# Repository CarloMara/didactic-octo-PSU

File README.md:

# **Didactic PSU**

**An efficient finals project**

So, @nicogela and I decided to build a LAB PSU, but because we're lazy people and we don't like to carry weight we're tring to unite the high efficiency of the switching topologies to the high stability and low noise of the linear ones.

Up until now we've designed the linear stage, and we added to it some DACs in oreder to controll it with a uC. The next stage in the design process will be the testing of the linear + the dacs. If everithing works we will go ahead adding to the desing the switching stage.

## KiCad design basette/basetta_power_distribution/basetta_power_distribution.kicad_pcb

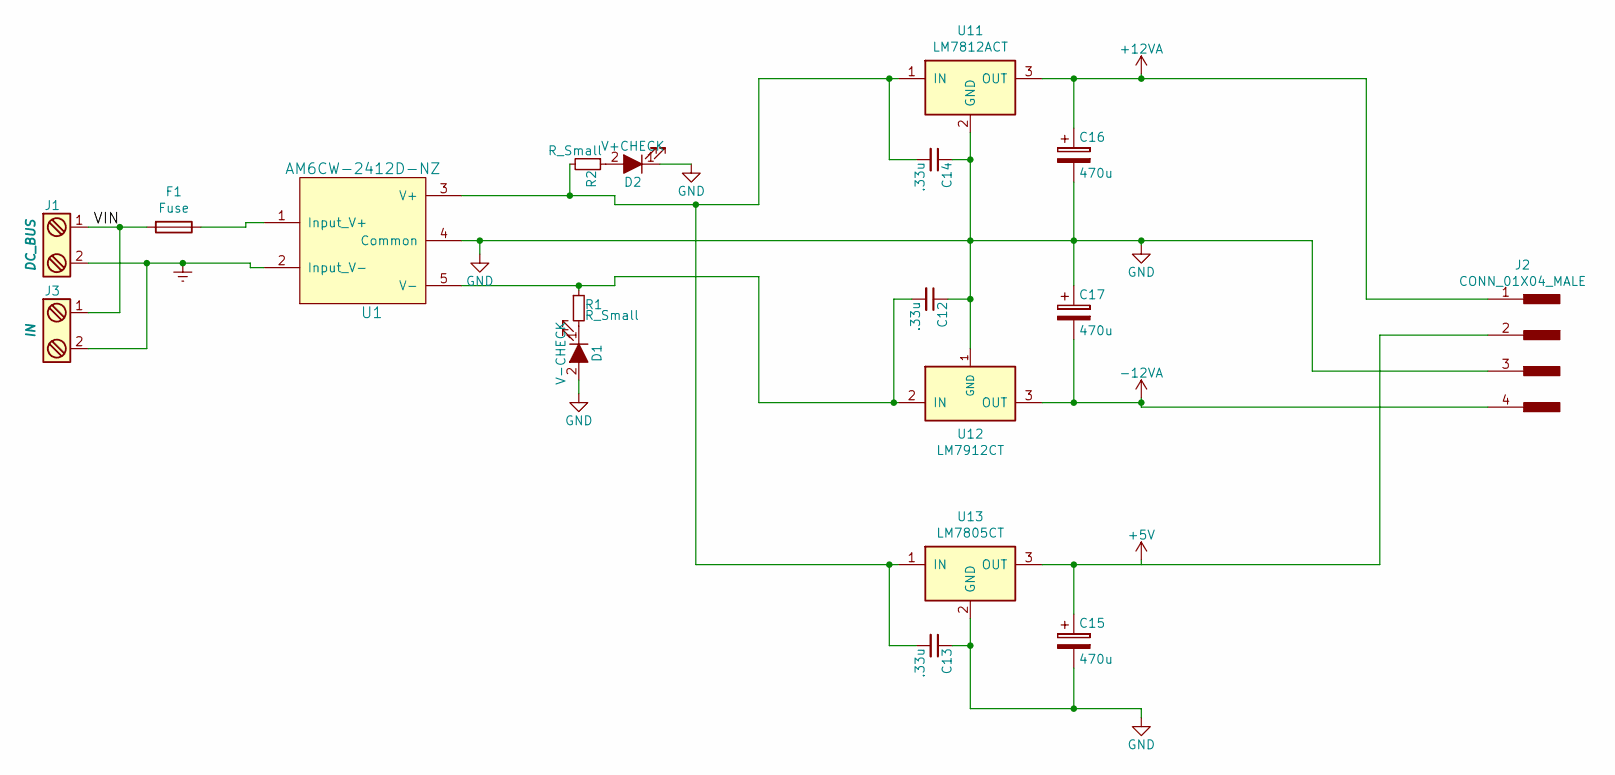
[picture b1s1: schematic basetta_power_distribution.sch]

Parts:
C12, C13, C14: .33u; C_Disc_D7.5mm_W5.0mm_P5.00mm; Voltage 50V
C15, C16, C17: 470u; CP_Radial_D8.0mm_P3.50mm; Voltage 50V
D1: V-CHECK; D_1206
D2: V+CHECK; D_1206
F1: Fuse; R_1210_HandSoldering
J1: DC_BUS; TerminalBlock_Pheonix_MPT-2.54mm_2pol
J2: CONN_01X04_MALE; Pin_Header_Straight_1x04_Pitch2.54mm
J3: IN; TerminalBlock_Pheonix_MPT-2.54mm_2pol
R1, R2: R_Small; R_1206_HandSoldering
U1: AM6CW-2412D-NZ; AM4CW-NZ
U11: LM7812ACT; TO-220_Vertical
U12: LM7912CT; TO-220_Vertical
U13: LM7805CT; TO-220_Vertical

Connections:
+12VA: C16.1, J2.1, U11.3 (OUT)
-12VA: C17.2, J2.4, U12.3 (OUT)
/VIN: F1.2, J1.1, J3.1
Earth: J1.2, J3.2, U1.2 (Input_V-)
GND: C12.1, C13.1, C14.1, C15.2, C16.2, C17.1, D1.2 (A), D2.1 (K), J2.3, U1.4 (Common), U11.2 (GND), U12.1 (GND), U13.2 (GND)
unnamed: C12.2, R1.1, U1.5 (V-), U12.2 (IN)
unnamed: C13.2, C14.2, R2.2, U1.3 (V+), U11.1 (IN), U13.1 (IN)
unnamed: C15.1, J2.2, U13.3 (OUT)
unnamed: D1.1 (K), R1.2
unnamed: D2.2 (A), R2.1
unnamed: F1.1, U1.1 (Input_V+)

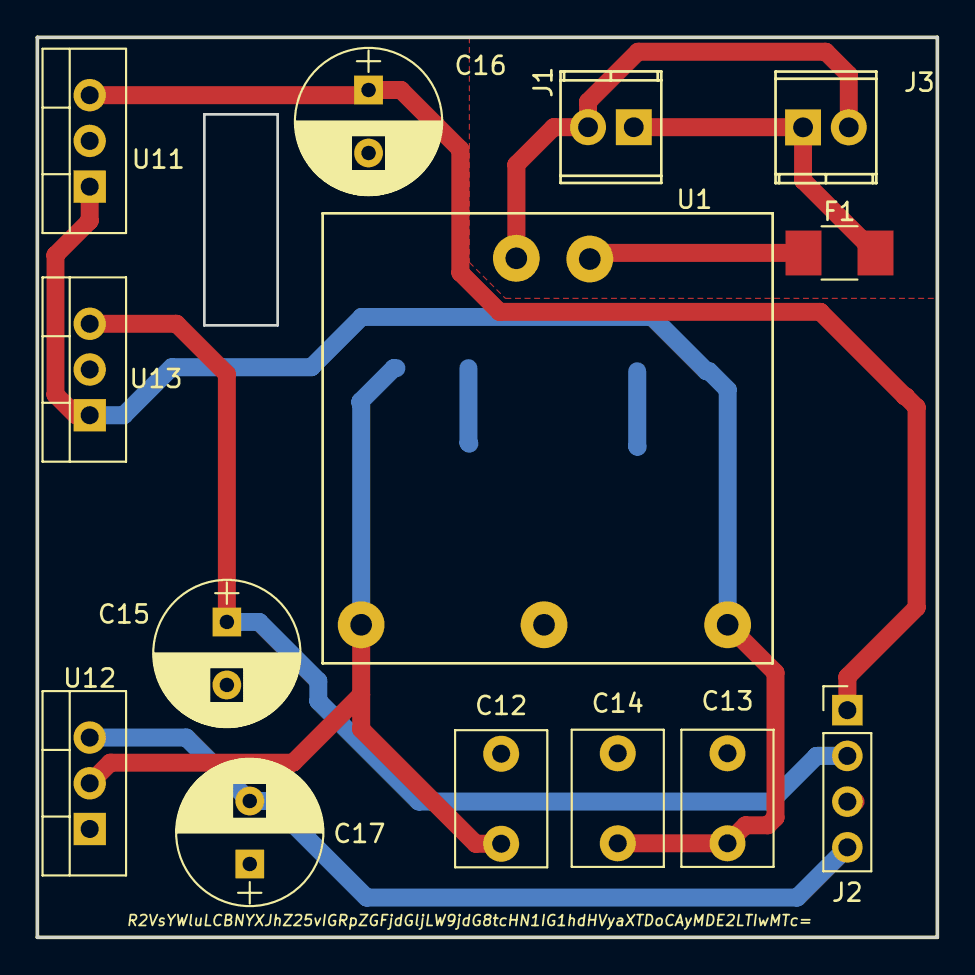
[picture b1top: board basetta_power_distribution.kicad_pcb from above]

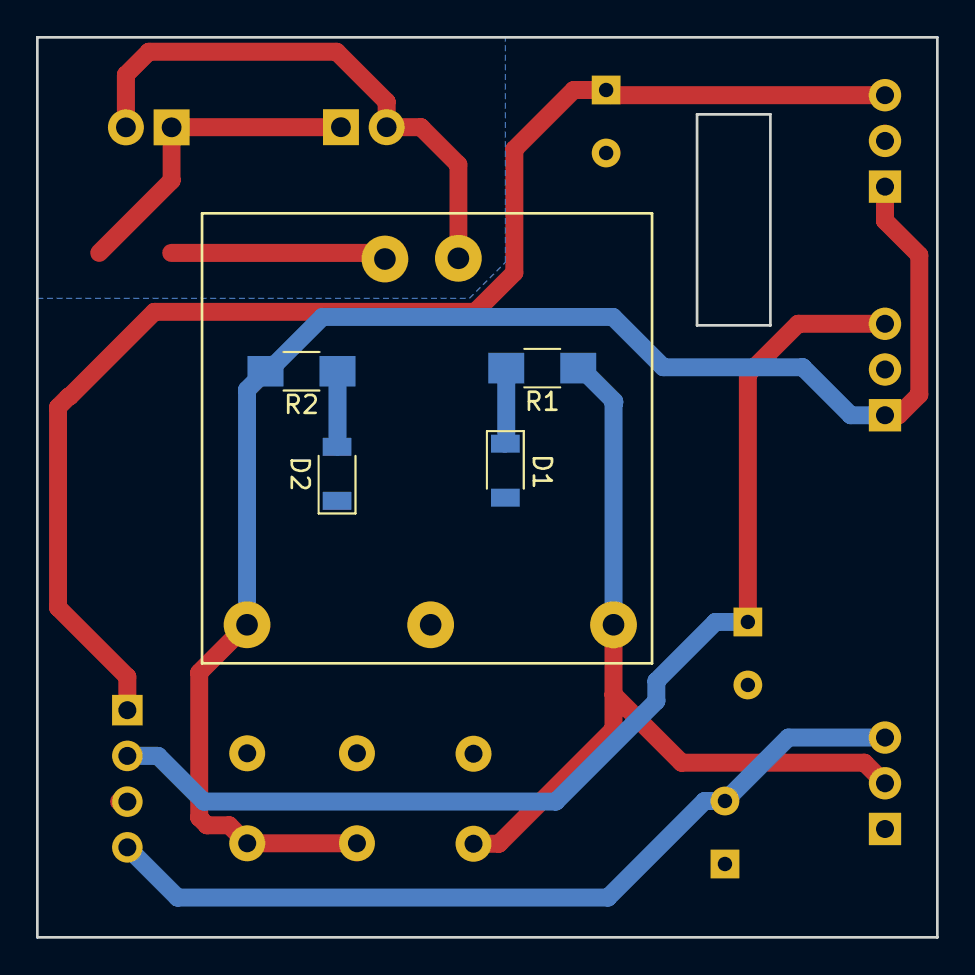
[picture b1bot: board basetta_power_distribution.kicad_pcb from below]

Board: 2 copper layers, 50.0 x 50.0 mm, 18 parts (4 on the bottom side), 11 nets.

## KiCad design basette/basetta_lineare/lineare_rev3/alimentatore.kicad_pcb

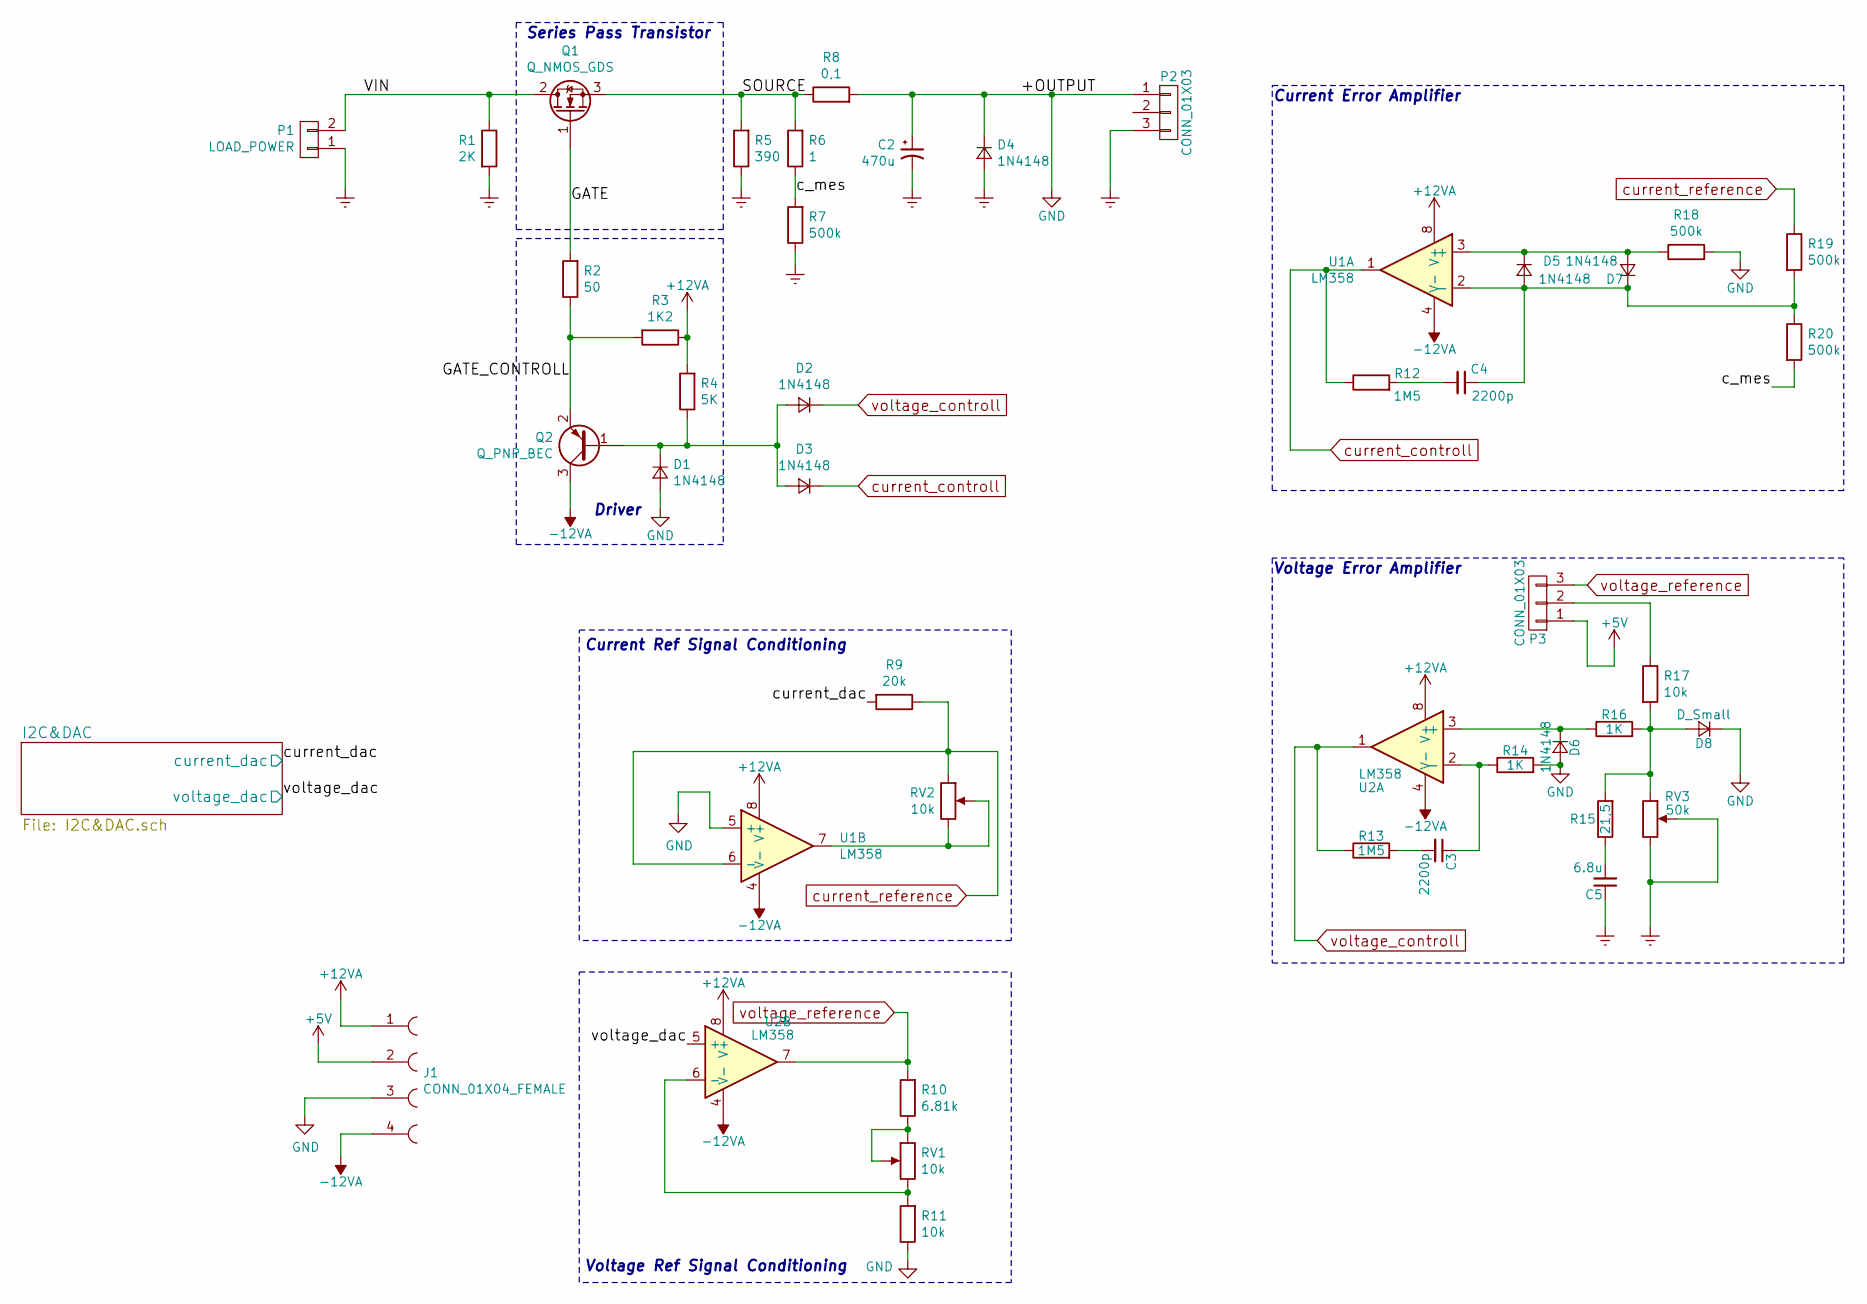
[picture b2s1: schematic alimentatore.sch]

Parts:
C2: 470u; CP_Radial_D14.0mm_P5.00mm; Voltage 50V
C3, C4: 2200p; C_0805; Voltage 50V
C5: 6.8u; C_0805; Voltage 35V
D1, D2, D3, D4, D5, D6, D7: 1N4148; D_0603
D8: D_Small; D_0603
J1: CONN_01X04_FEMALE; Pin_Header_Straight_1x04_Pitch2.54mm
P1: LOAD_POWER; TerminalBlock_Pheonix_MPT-2.54mm_2pol
P2: CONN_01X03; TerminalBlock_Pheonix_MPT-2.54mm_3pol
P3: CONN_01X03; Pin_Header_Straight_1x03_Pitch2.54mm
Q1: Q_NMOS_GDS; TO-220_Vertical
Q2: Q_PNP_BEC; SOT-23
R1: 2K; R_1206_HandSoldering
R2: 50; R_1206_HandSoldering
R3: 1K2; R_1206_HandSoldering
R4: 5K; R_1206_HandSoldering
R5: 390; R_1206_HandSoldering
R6: 1; R_1206_HandSoldering
R7, R18, R19, R20: 500k; R_1206_HandSoldering
R8: 0,1; R_2512_HandSoldering
R9: 20k; R_1206_HandSoldering
R10: 6.81k; R_1206_HandSoldering
R11, R17: 10k; R_1206_HandSoldering
R12, R13: 1M5; R_1206_HandSoldering
R14, R16: 1K; R_1206_HandSoldering
R15: 21,5; R_1206_HandSoldering
RV1, RV2: 10k; SR_Passive
RV3: 50k; SR_Passive
U1, U2: LM358; SO-8

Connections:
+12VA: J1.1, R3.1, R4.2, U1.8 (V+), U2.8 (V+)
-12VA: J1.4, Q2.3 (C), U1.4 (V-), U2.4 (V-)
/GATE: Q1.1 (G), R2.2
/GATE_CONTROLL: Q2.2 (E), R2.1, R3.2
/SOURCE: Q1.3 (S), R5.2, R6.2, R8.1
/VIN: P1.2, Q1.2 (D), R1.1
/c_mes: R6.1, R7.2, R20.2
Earth: C2.2, C5.1, D4.2 (A), P1.1, P2.3, R1.2, R5.1, R7.1, RV3.2, RV3.3
unnamed: C3.1, R14.1, U2.2 (-)
unnamed: C3.2, R13.2
unnamed: C4.1, D5.2 (A), D7.1 (K), R19.2, R20.1, U1.2 (-)
unnamed: C4.2, R12.2
unnamed: C5.2, R15.1
unnamed: D1.1 (K), D2.2 (A), D3.2 (A), Q2.1 (B), R4.1
unnamed: D5.1 (K), D7.2 (A), R18.1, U1.3 (+)
unnamed: D6.1 (K), R16.1, U2.3 (+)
unnamed: D8.2 (A), R15.2, R16.2, R17.2, RV3.1
unnamed: P3.2, R17.1
unnamed: R10.1, RV1.1, RV1.2
unnamed: R11.2, RV1.3, U2.6 (-)
unnamed: RV2.2, RV2.3, U1.7
current_controll: D3.1 (K), R12.1, U1.1
current_reference: R9.1, R19.1, RV2.1, U1.6 (-)
voltage_controll: D2.1 (K), R13.1, U2.1
voltage_reference: P3.3, R10.2, U2.7

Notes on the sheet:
Voltage Error Amplifier
Driver
Series Pass Transistor
Current Error Amplifier
Current Ref Signal Conditioning
Voltage Ref Signal Conditioning

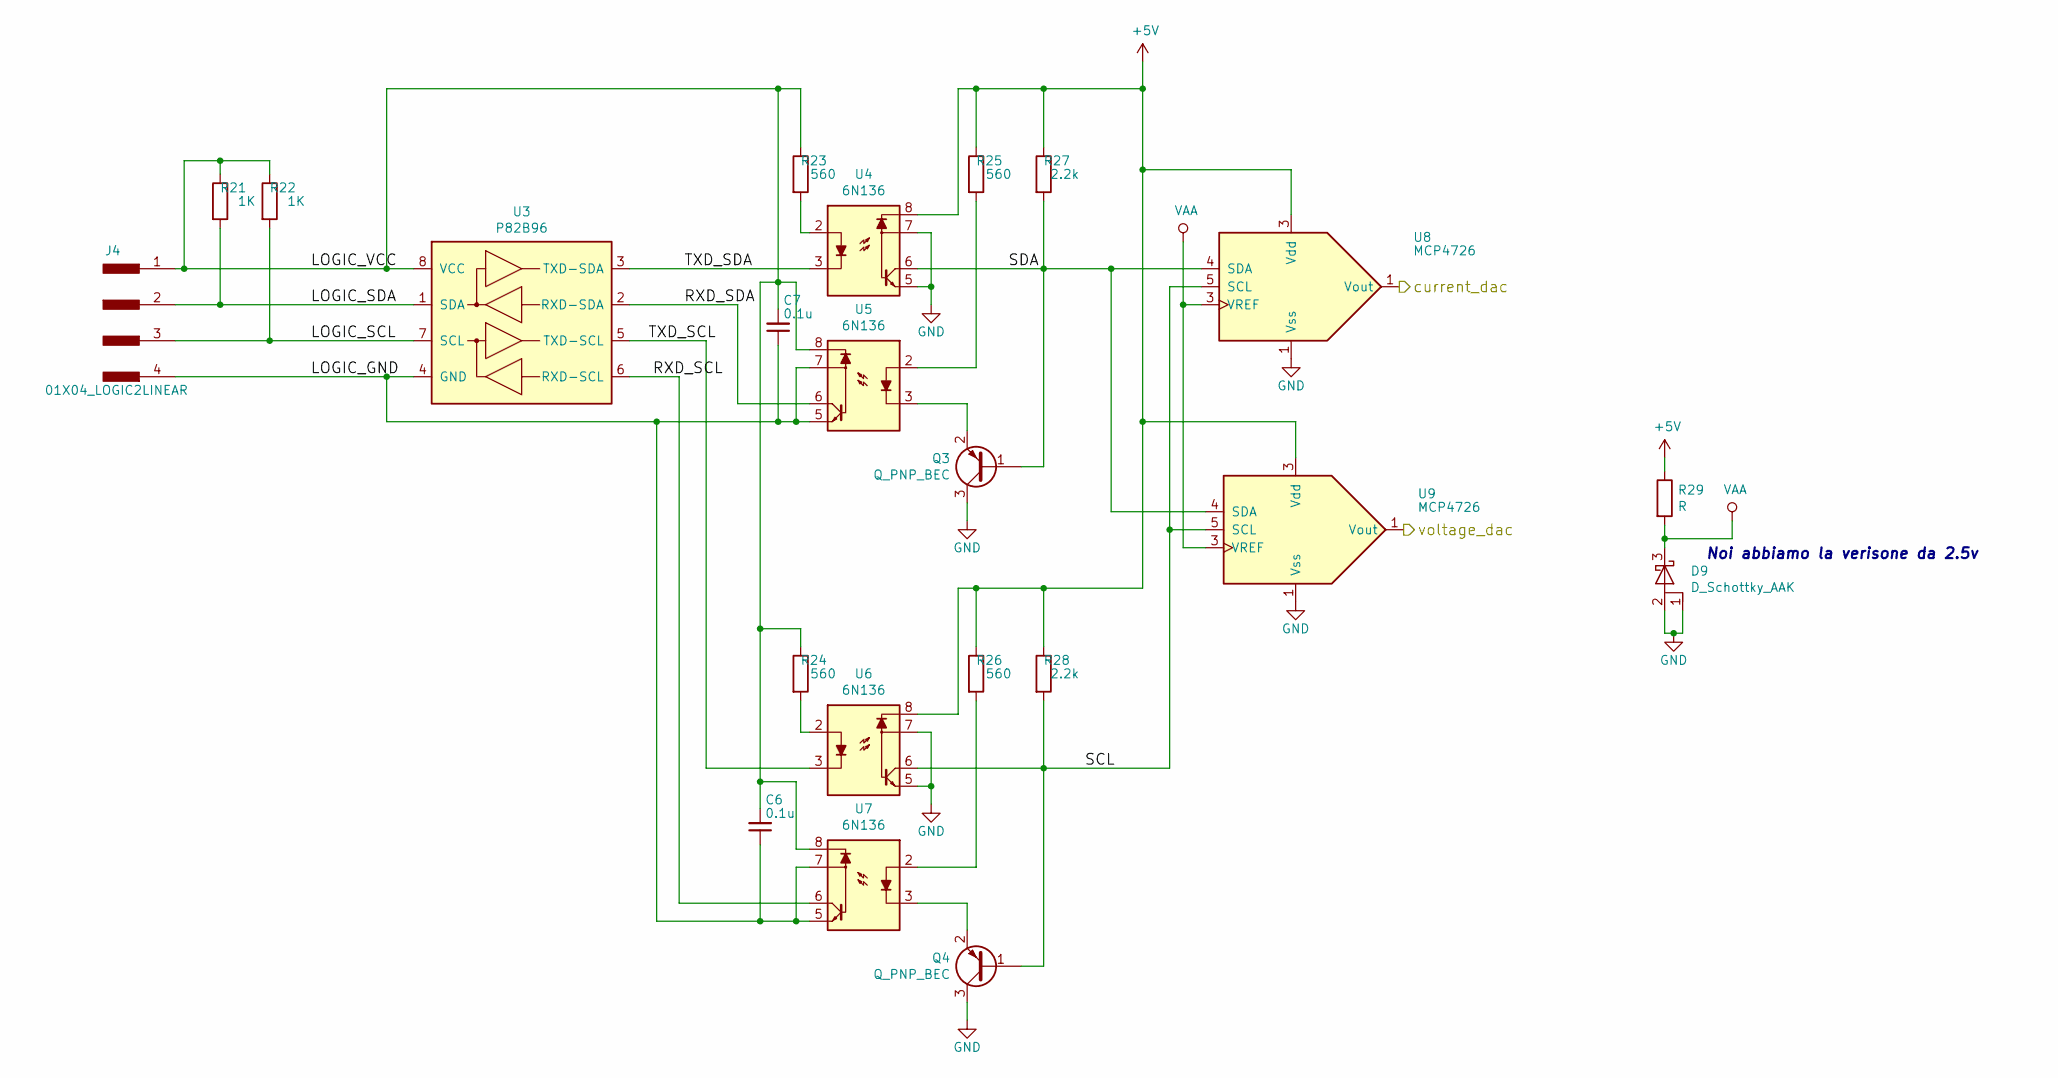
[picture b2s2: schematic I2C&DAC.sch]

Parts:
C6, C7: 0.1u; C_0805; Voltage 35V
D9: D_Schottky_AAK; SOT-23
J4: 01X04_LOGIC2LINEAR; Pin_Header_Straight_1x04_Pitch2.54mm
Q3, Q4: Q_PNP_BEC; SOT-23
R21, R22: 1K; R_1206_HandSoldering
R23, R24, R25, R26: 560; R_1206_HandSoldering
R27, R28: 2.2k; R_1206_HandSoldering
R29: R; R_1206_HandSoldering
U3: P82B96; SO-8
U4, U5, U6, U7: 6N136; SO-8
U8, U9: MCP4726; SOT-23-6_Handsoldering

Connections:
/I2C&DAC/LOGIC_GND: C6.1, C7.1, J4.4, U3.4 (GND), U5.5, U5.7, U7.5, U7.7
/I2C&DAC/LOGIC_SCL: J4.3, R22.2, U3.7 (SCL)
/I2C&DAC/LOGIC_SDA: J4.2, R21.2, U3.1 (SDA)
/I2C&DAC/LOGIC_VCC: C6.2, C7.2, J4.1, R21.1, R22.1, R23.1, R24.1, U3.8 (VCC), U5.8, U7.8
/I2C&DAC/RXD_SCL: U3.6 (RXD-SCL), U7.6
/I2C&DAC/RXD_SDA: U3.2 (RXD-SDA), U5.6
/I2C&DAC/SCL: Q4.1 (B), R28.2, U6.6, U8.5 (SCL), U9.5 (SCL)
/I2C&DAC/SDA: Q3.1 (B), R27.2, U4.6, U8.4 (SDA), U9.4 (SDA)
/I2C&DAC/TXD_SCL: U3.5 (TXD-SCL), U6.3
/I2C&DAC/TXD_SDA: U3.3 (TXD-SDA), U4.3
unnamed: Q3.2 (E), U5.3
unnamed: Q4.2 (E), U7.3
unnamed: R23.2, U4.2
unnamed: R24.2, U6.2
unnamed: R25.2, U5.2
unnamed: R26.2, U7.2

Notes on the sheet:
Noi abbiamo la verisone da 2.5v

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
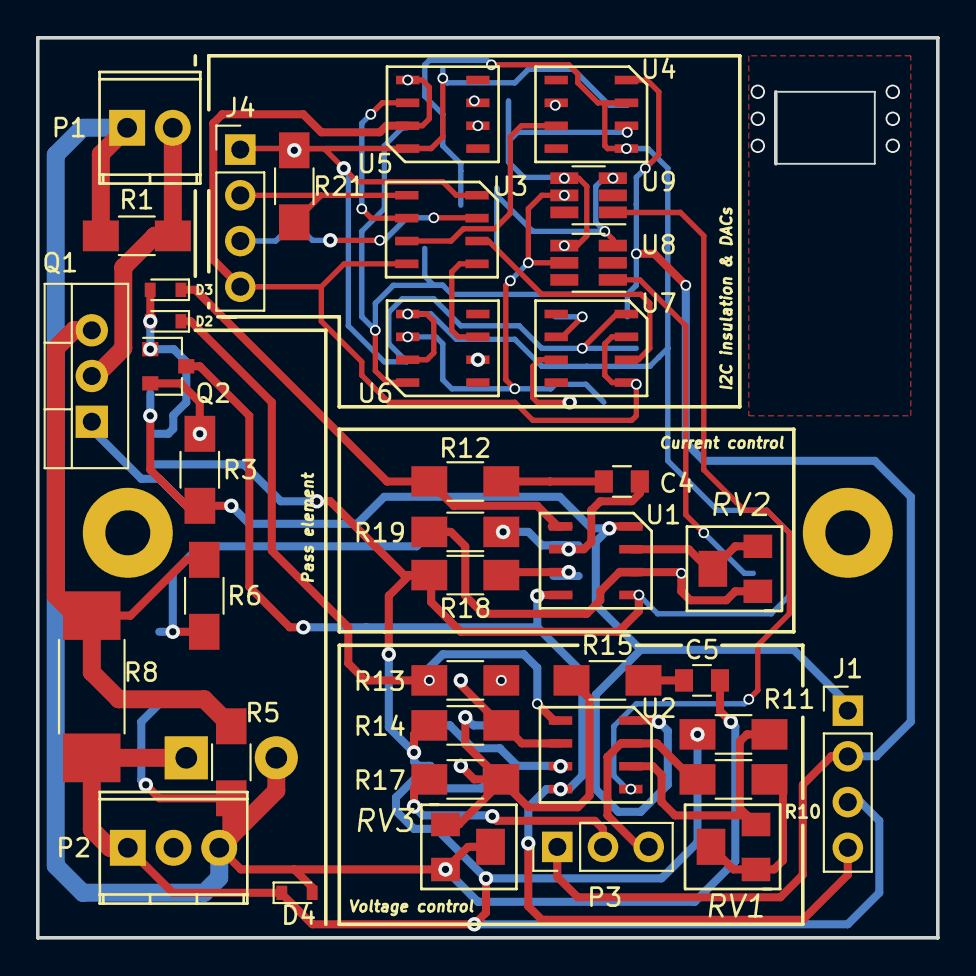
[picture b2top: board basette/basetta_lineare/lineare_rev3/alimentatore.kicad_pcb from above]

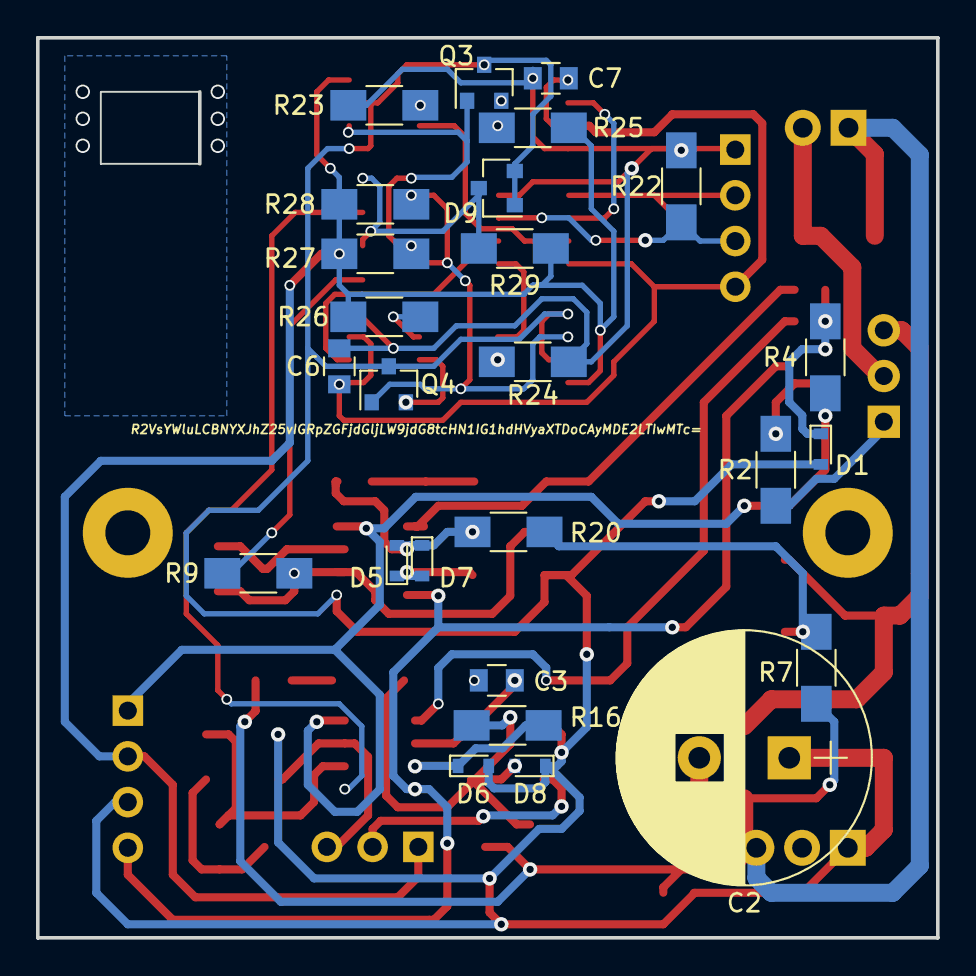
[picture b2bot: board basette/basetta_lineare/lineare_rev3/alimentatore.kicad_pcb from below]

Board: 2 copper layers, 50.0 x 50.0 mm, 65 parts (26 on the bottom side), 46 nets.

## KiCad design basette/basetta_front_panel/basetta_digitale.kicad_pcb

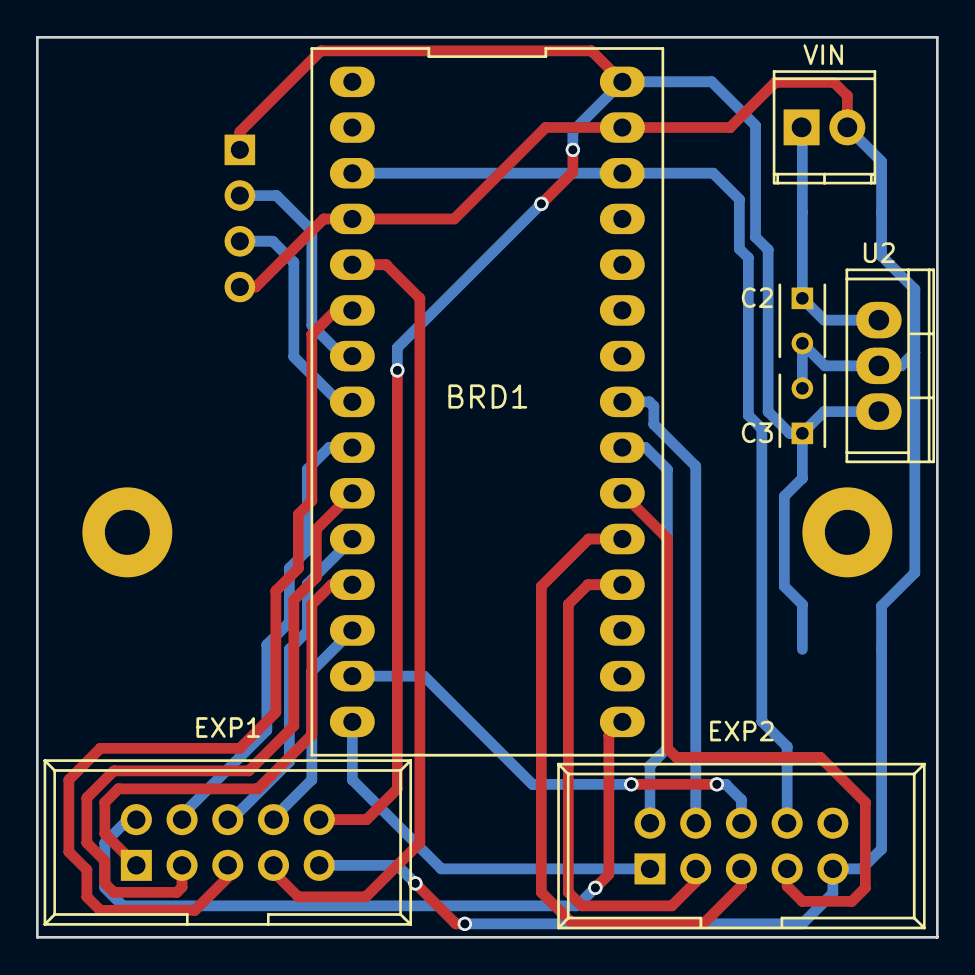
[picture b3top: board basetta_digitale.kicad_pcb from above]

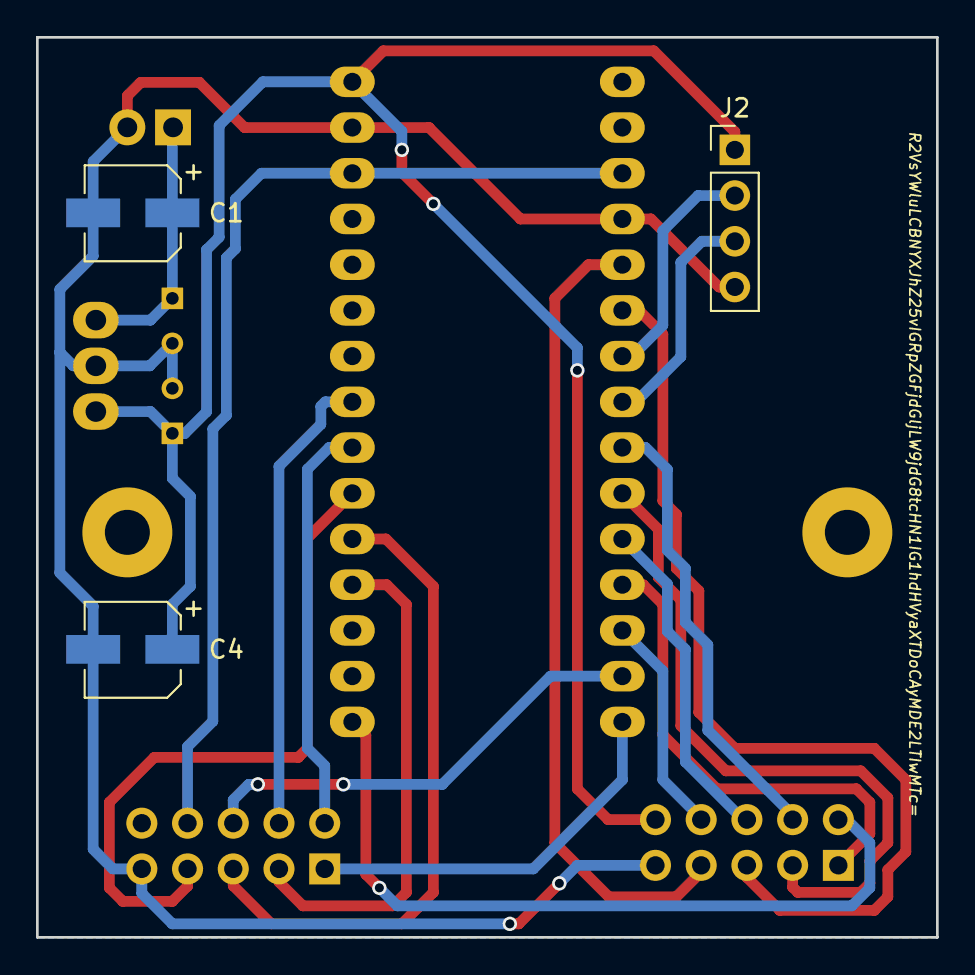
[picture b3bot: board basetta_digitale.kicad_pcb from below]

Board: 2 copper layers, 50.0 x 50.0 mm, 10 parts (3 on the bottom side), 21 nets.

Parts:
BRD1: NUCLEO_F3030K8; DIP-30_0_ELL
C1, C4: CP; CP_Elec_5x5.3
C2, C3: C; C_Rect_L4_W2.5_P2.5
EXP1, EXP2: CONN_02X05; IDC_Header_Straight_10pins
J2: CONN_01X04_FEMALE; Pin_Header_Straight_1x04_Pitch2.54mm
U2: LM7805CT; TO-220
VIN: LOGIC_VIN; TerminalBlock_Pheonix_MPT-2.54mm_2pol

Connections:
+5V: BRD1.30, C3.1, C4.1, EXP1.10, J2.1, U2.3
/BTN_EN1: BRD1.20, EXP2.5
/BTN_EN2: BRD1.19, EXP2.3
/BTN_ENC: BRD1.16, EXP1.2
/Beeper: BRD1.12, EXP1.1
/LCD4: BRD1.6, EXP1.5
/LCD5: BRD1.11, EXP1.6
/LCD6: BRD1.5, EXP1.7
/LCD7: BRD1.13, EXP1.8
/LCDE: BRD1.10, EXP1.3
/LCDRS: BRD1.9, EXP1.4
/MISO: BRD1.15, EXP2.1
/MOSI: BRD1.14, EXP2.6
/RESET: BRD1.3, BRD1.28, EXP2.8
/SCK: BRD1.22, EXP2.2
/SCL: BRD1.8, J2.3
/SDA: BRD1.7, J2.2
/SD_CSEL: BRD1.23, EXP2.4
/SD_DET: BRD1.21, EXP2.7
/VIN: C1.1, C2.1, U2.1, VIN.1
GND: BRD1.4, BRD1.29, C1.2, C2.2, C3.2, C4.2, EXP1.9, EXP2.9, J2.4, U2.2, VIN.2

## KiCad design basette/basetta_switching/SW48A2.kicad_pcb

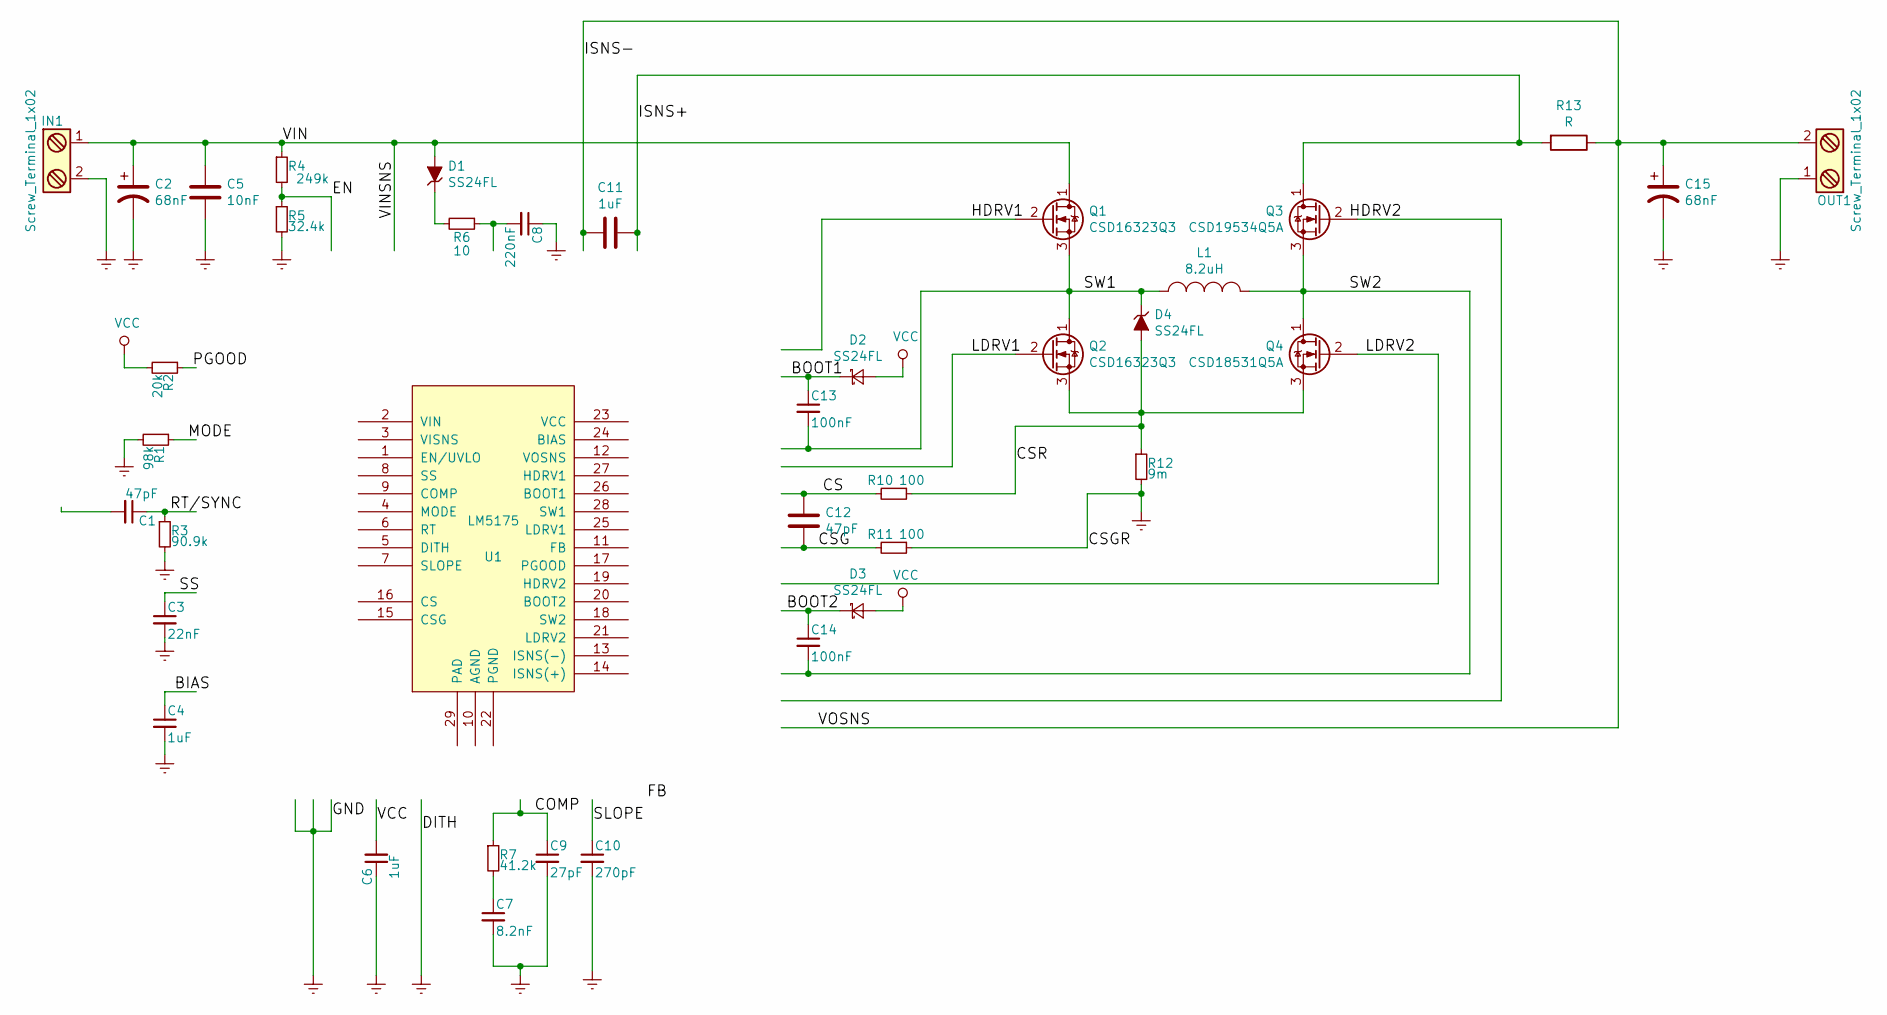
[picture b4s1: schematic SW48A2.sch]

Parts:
C1, C12: 47pF; C_Disc_D3.8mm_W2.6mm_P2.50mm
C2, C15: 68nF; CP_Elec_6.3x5.3
C3: 22nF; C_Disc_D3.8mm_W2.6mm_P2.50mm
C4, C6, C11: 1uF; C_Disc_D3.8mm_W2.6mm_P2.50mm
C5: 10nF; C_Disc_D3.8mm_W2.6mm_P2.50mm
C7: 8.2nF; C_Disc_D3.8mm_W2.6mm_P2.50mm
C8: 220nF; C_Disc_D3.8mm_W2.6mm_P2.50mm
C9: 27pF; C_Disc_D3.8mm_W2.6mm_P2.50mm
C10: 270pF; C_Disc_D3.8mm_W2.6mm_P2.50mm
C13, C14: 100nF; C_Disc_D3.8mm_W2.6mm_P2.50mm
D1, D2, D3, D4: SS24FL; D_SOD-123
IN1: Screw_Terminal_1x02; TerminalBlock_Pheonix_MPT-2.54mm_2pol
L1: 8.2uH; coil_craft
OUT1: Screw_Terminal_1x02; TerminalBlock_Pheonix_MPT-2.54mm_2pol
Q1, Q2: CSD16323Q3
Q3: CSD19534Q5A
Q4: CSD18531Q5A; CSD19534Q5A
R1: 98k; R_1206_HandSoldering
R2: 20k; R_1206_HandSoldering
R3: 90.9k; R_1206_HandSoldering
R4: 249k; R_1206_HandSoldering
R5: 32.4k; R_1206_HandSoldering
R6: 10; R_1206_HandSoldering
R7: 41.2k; R_1206_HandSoldering
R10, R11: 100; R_1206_HandSoldering
R12: 9m; R_1206_HandSoldering
R13: R; R_1206_HandSoldering
U1: LM5175; SOP65P640X120-28N

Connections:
/BIAS: C4.1, U1.24 (BIAS)
/BOOT1: C13.1, D2.1 (K), U1.26 (BOOT1)
/BOOT2: C14.1, D3.1 (K), U1.20 (BOOT2)
/COMP: C9.1, R7.1, U1.9 (COMP)
/CS: C12.1, R10.2, U1.16 (CS)
/CSG: C12.2, R11.2, U1.15 (CSG)
/CSR: D4.2 (A), Q2.3 (S), Q4.3 (S), R10.1, R12.1
/EN: R4.2, R5.1, U1.1 (EN/UVLO)
/FB: U1.11 (FB)
/HDRV1: Q1.2 (G), U1.27 (HDRV1)
/HDRV2: Q3.2 (G), U1.19 (HDRV2)
/ISNS+: C11.1, Q3.1 (D), R13.2, U1.14 (ISNS(+))
/ISNS-: C11.2, C15.1, OUT1.2, R13.1, U1.12 (VOSNS), U1.13 (ISNS(-))
/LDRV1: Q2.2 (G), U1.25 (LDRV1)
/LDRV2: Q4.2 (G), U1.21 (LDRV2)
/MODE: R1.1, U1.4 (MODE)
/PGOOD: R2.1, U1.17 (PGOOD)
/RT/SYNC: C1.1, R3.1, U1.6 (RT)
/SLOPE: C10.1, U1.7 (SLOPE)
/SS: C3.1, U1.8 (SS)
/SW1: C13.2, D4.1 (K), L1.1, Q1.3 (S), Q2.1 (D), U1.28 (SW1)
/SW2: C14.2, L1.2, Q3.3 (S), Q4.1 (D), U1.18 (SW2)
/VIN: C2.1, C5.1, D1.2 (A), IN1.1, Q1.1 (D), R4.1, U1.3 (VISNS)
Earth: C2.2, C3.2, C4.2, C5.2, C6.1, C7.2, C8.1, C9.2, C10.2, C15.2, IN1.2, OUT1.1, R1.2, R3.2, R5.2, R11.1, R12.2, U1.5 (DITH), U1.10 (AGND), U1.22 (PGND), U1.29 (PAD)
unnamed: C7.1, R7.2
unnamed: D1.1 (K), R6.2
VCC: C6.2, D2.2 (A), D3.2 (A), R2.2, U1.23 (VCC)

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
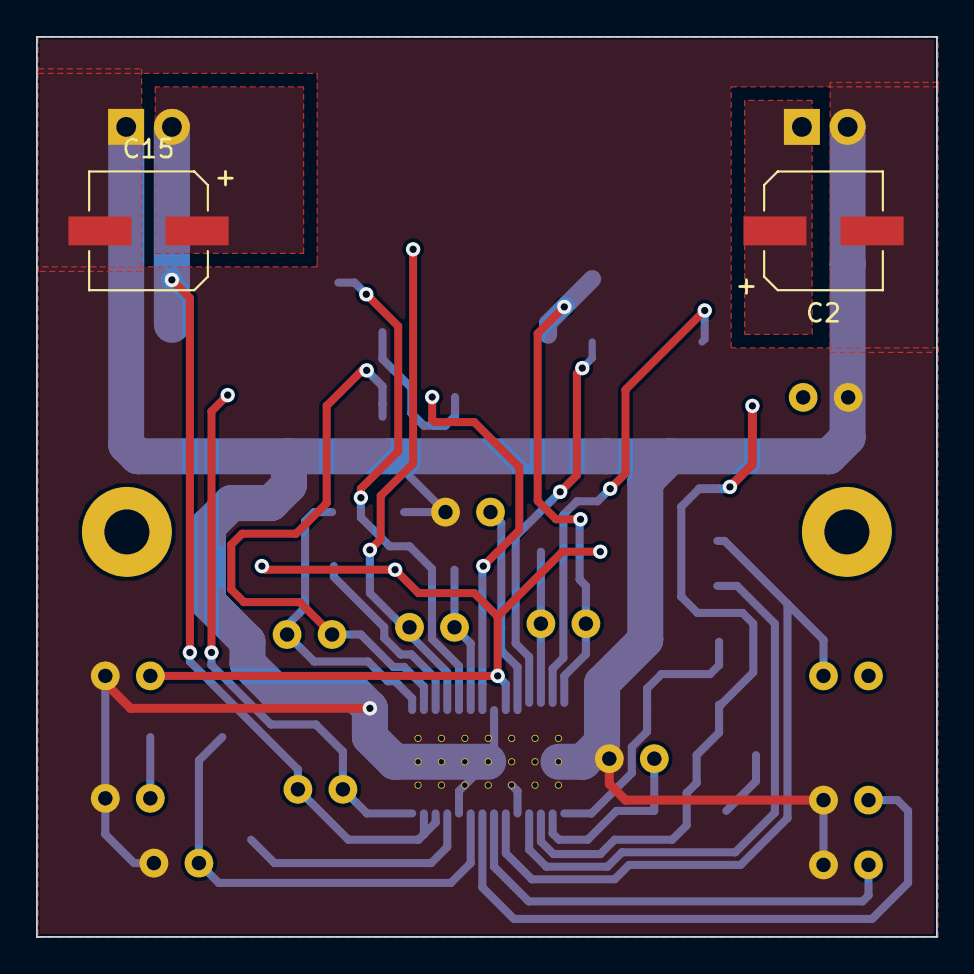
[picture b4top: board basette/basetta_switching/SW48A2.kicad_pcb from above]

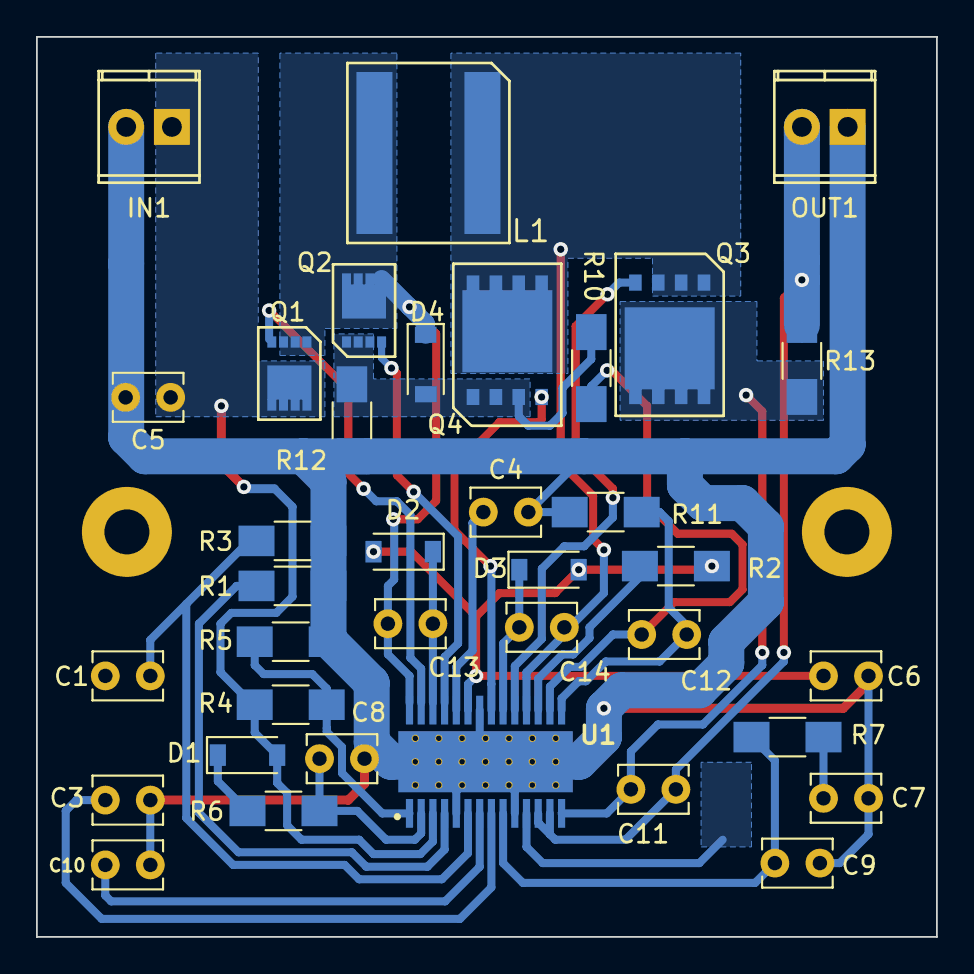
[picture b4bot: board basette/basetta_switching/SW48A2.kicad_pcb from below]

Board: 2 copper layers, 50.0 x 50.0 mm, 38 parts (36 on the bottom side), 27 nets.

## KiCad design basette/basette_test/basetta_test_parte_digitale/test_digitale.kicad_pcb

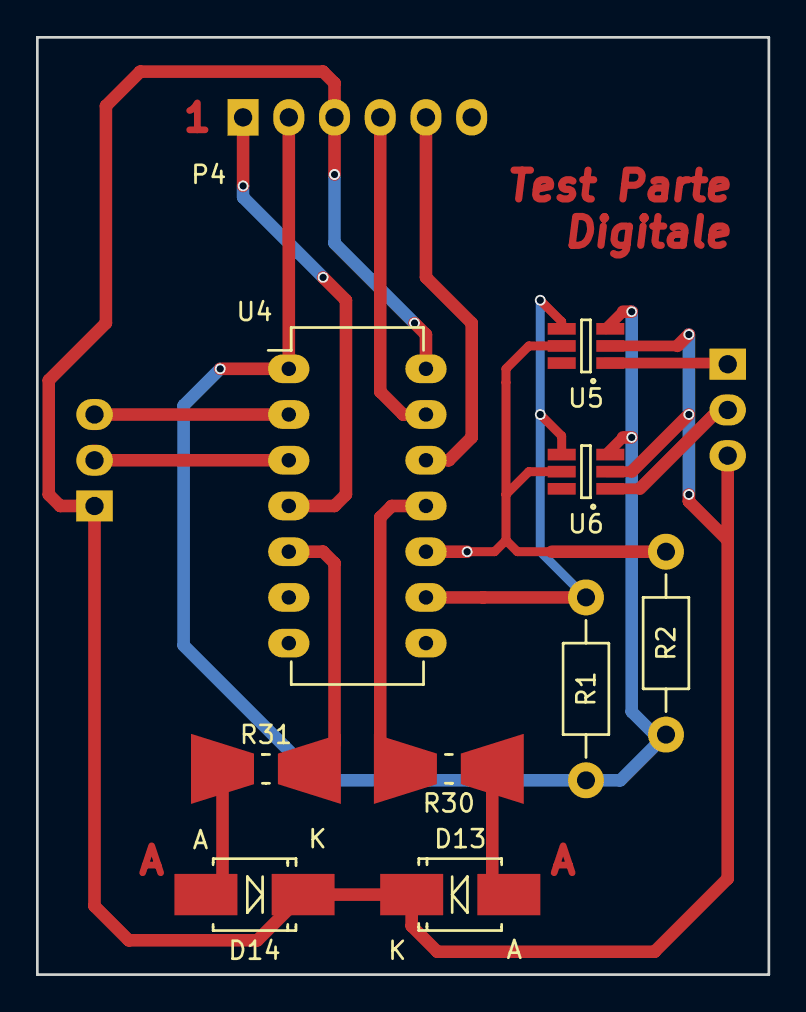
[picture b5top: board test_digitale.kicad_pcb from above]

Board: 2 copper layers, 40.6 x 52.1 mm, 12 parts (0 on the bottom side), 16 nets.

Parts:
D13, D14: Led_Small; SMB_Handsoldering
P1: CONN_01X03; Pin_Header_Straight_1x03
P3: UART_01X03; Pin_Header_Straight_1x03
P4: ICSP_01X06; Pin_Header_Straight_1x06
R1, R2: R; Resistor_Horizontal_RM10mm
R30, R31: 390; Resistor_SMD+THTuniversal_0805to2512_HandSoldering
U4: PIC16F18323; DIP-14_W7.62mm_LongPads
U5, U6: MCP4726; SOT-23-6_Handsoldering

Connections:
+5V: P4.2, R1.1, R2.1, U4.1, U5.3, U6.3
/ICSPCLK: P4.5, U4.12
/ICSPDAT: P4.4, U4.13
/RX: P3.3, U4.2
/SCL: R2.2, U4.10, U5.5, U6.5
/SDA: R1.2, U4.9, U5.4, U6.4
/STATUS_LED_1: R31.2, U4.5
/STATUS_LED_2: R30.2, U4.11
/TX: P3.2, U4.3
/dac_1_out: P1.1, U5.1
/dac_2_out: P1.2, U6.1
/~MCLR: P4.1, U4.4
GND: D13.1, D14.1, P1.3, P3.1, P4.3, U4.14, U5.2, U6.2
unnamed: D13.2, R30.1
unnamed: D14.2, R31.1
VAA: U5.6, U6.6
